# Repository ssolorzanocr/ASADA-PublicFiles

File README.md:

LoRa based control and log system for ASADA-Samara
============

### Most recent version of this repository can be found in: ###

* [ASADA-PublicFiles](https://github.com/ssolorzanocr/ASADA-PublicFiles)

### What is this repository for? ###

* This repository was created to develop LoRa based embedded control solution for the pumps of ASADA-Samara. 

### HELTEC LoRa 32 board information

* [Documentation page](https://heltec.org/project/wifi-lora-32/)
* [Pinout diagram](https://resource.heltec.cn/download/WiFi_LoRa_32/WIFI_LoRa_32_V2.pdf)
* [Schematic](https://resource.heltec.cn/download/WiFi_LoRa_32/V2/WIFI_LoRa_32_V2(868-915).PDF)
* [ESP32 datasheet](https://www.espressif.com/sites/default/files/documentation/esp32_datasheet_en.pdf) 

### Enclousure

* [Page](https://www.se.com/es/es/product/NSYCRN33200P/spacial-crn-plain-door-with-mount.plate.-h300xw300xd200-ip66-ik10-ral7035../) 

### How do I get set up? ###

* Install Git
* Install Arduino IDE
* Install Heltec ESP32 Library in the Arduino Library Manager
Open Arduino IDE, then Select `Sketch`->`Include Library`->`Manage Libraries...`
Search `Heltec ESP32` and install it.
* Install Adafruit MQTT Library in the Arduino Library Manager
Open Arduino IDE, then Select `Sketch`->`Include Library`->`Manage Libraries...`
Search `Adafruit MQTT` and install it.

### Library source code and examples
* [Adafruit_MQTT_Library](https://github.com/adafruit/Adafruit_MQTT_Library)

### Contribution guidelines ###

* If you want to propose a review or need to modify the code for any reason first clone this [repository](https://github.com/ssolorzanocr/ASADA-PublicFiles) in your PC and create a new branch for your changes. Once your changes are complete and fully tested ask the administrator permission to push this new branch into the source.
* If you just want to do local changes instead you can download a zip version of the repository and do all changes locally in your PC. 

### Who do I talk to? ###

* [Juan J. Rojas](mailto:juan.rojas@itcr.ac.cr)
* [Sergio Solorzano](mailto:solorzanos117@gmail.com)

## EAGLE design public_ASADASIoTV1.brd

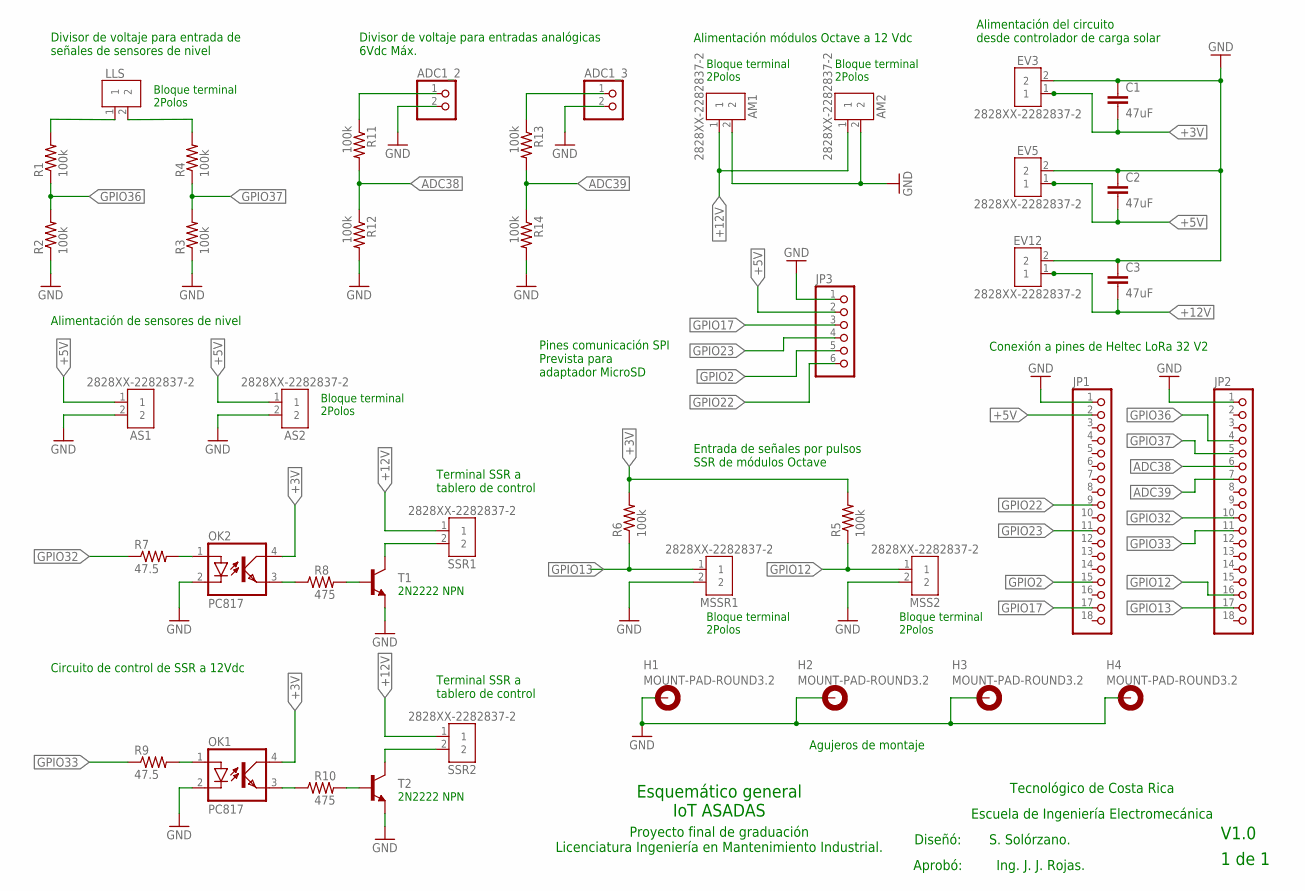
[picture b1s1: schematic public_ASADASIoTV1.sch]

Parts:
ADC1_2, ADC1_3: PINHD-1X2; 1X02
AM1, AM2: 2828XX-2282837-2; TERMBLK_508-2N
AS1, AS2: 2828XX-2282837-2; TERMBLK_508-2N
C1, C2, C3: 47uF; C2.5-5
EV3, EV5, EV12: 2828XX-2282837-2; TERMBLK_508-2N
H1, H2, H3, H4: MOUNT-PAD-ROUND3.2; 3,2-PAD
JP1, JP2: PINHD-1X18; 1X18
JP3: PINHD-1X6; 1X06
LLS: 2828XX-2282837-2; TERMBLK_508-2N
MSS2: 2828XX-2282837-2; TERMBLK_508-2N
MSSR1: 2828XX-2282837-2; TERMBLK_508-2N
OK1, OK2: PC817; DIL04
R1, R2, R3, R4, R5, R6, R11, R12, R13, R14: 100k; R0805
R7, R9: 47.5; R0805
R8, R10: 475; R0805
SSR1, SSR2: 2828XX-2282837-2; TERMBLK_508-2N
T1, T2: 2N3904; TO92

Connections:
+3V: C1.2, EV3.1, OK1.4 (COL), OK2.4 (COL), R5.2, R6.2
+5V: AS1.1, AS2.1, C2.2, EV5.1, JP1.2, JP3.2
+12V: AM1.1, AM2.1, C3.2, EV12.1, SSR1.1, SSR2.1
ADC38: JP2.6, R11.2, R12.1
ADC39: JP2.7, R13.2, R14.1
GND: ADC1_2.2, ADC1_3.2, AM1.2, AM2.2, AS1.2, AS2.2, C1.1, C2.1, C3.1, EV3.2, EV5.2, EV12.2, H1.B3,2, H2.B3,2, H3.B3,2, H4.B3,2, JP1.1, JP2.1, JP3.1, MSS2.2, MSSR1.2, OK1.2 (C), OK2.2 (C), R2.1, R3.1, R12.2, R14.2, T1.3 (E), T2.3 (E)
GPIO2: JP1.15, JP3.5
GPIO12: JP2.16, MSS2.1, R5.1
GPIO13: JP2.17, MSSR1.1, R6.1
GPIO17: JP1.17, JP3.3
GPIO22: JP1.9, JP3.6
GPIO23: JP1.11, JP3.4
GPIO32: JP2.10, R7.1
GPIO33: JP2.11, R9.1
GPIO36: JP2.4, R1.1, R2.2
GPIO37: JP2.5, R3.2, R4.1
HLS: LLS.2, R4.2
LLS: LLS.1, R1.2
unnamed: OK2.1 (A), R7.2
unnamed: SSR1.2, T1.1 (C)
unnamed: R8.2, T1.2 (B)
unnamed: OK2.3 (EMIT), R8.1
unnamed: ADC1_3.1, R13.1
unnamed: ADC1_2.1, R11.1
unnamed: OK1.1 (A), R9.2
unnamed: R10.2, T2.2 (B)
unnamed: OK1.3 (EMIT), R10.1
unnamed: SSR2.2, T2.1 (C)

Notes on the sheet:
Terminal SSR a tablero de control
Entrada de señales por pulsos SSR de módulos Octave
Alimentación de sensores de nivel
Divisor de voltaje para entrada de señales de sensores de nivel
Alimentación módulos Octave a 12 Vdc
Divisor de voltaje para entradas analógicas 6Vdc Máx.
Alimentación del circuito desde controlador de carga solar
Pines comunicación SPI Prevista para adaptador MicroSD
Agujeros de montaje
Conexión a pines de Heltec LoRa 32 V2
Circuito de control de SSR a 12Vdc
V1.0
1 de 1
Proyecto final de graduación Licenciatura Ingeniería en Mantenimiento Industrial.
Diseñó:
S. Solórzano.
Aprobó:
Ing. J. J. Rojas.
Escuela de Ingeniería Electromecánica
Tecnológico de Costa Rica
Esquemático general IoT ASADAS
2N2222 NPN
Bloque terminal 2Polos

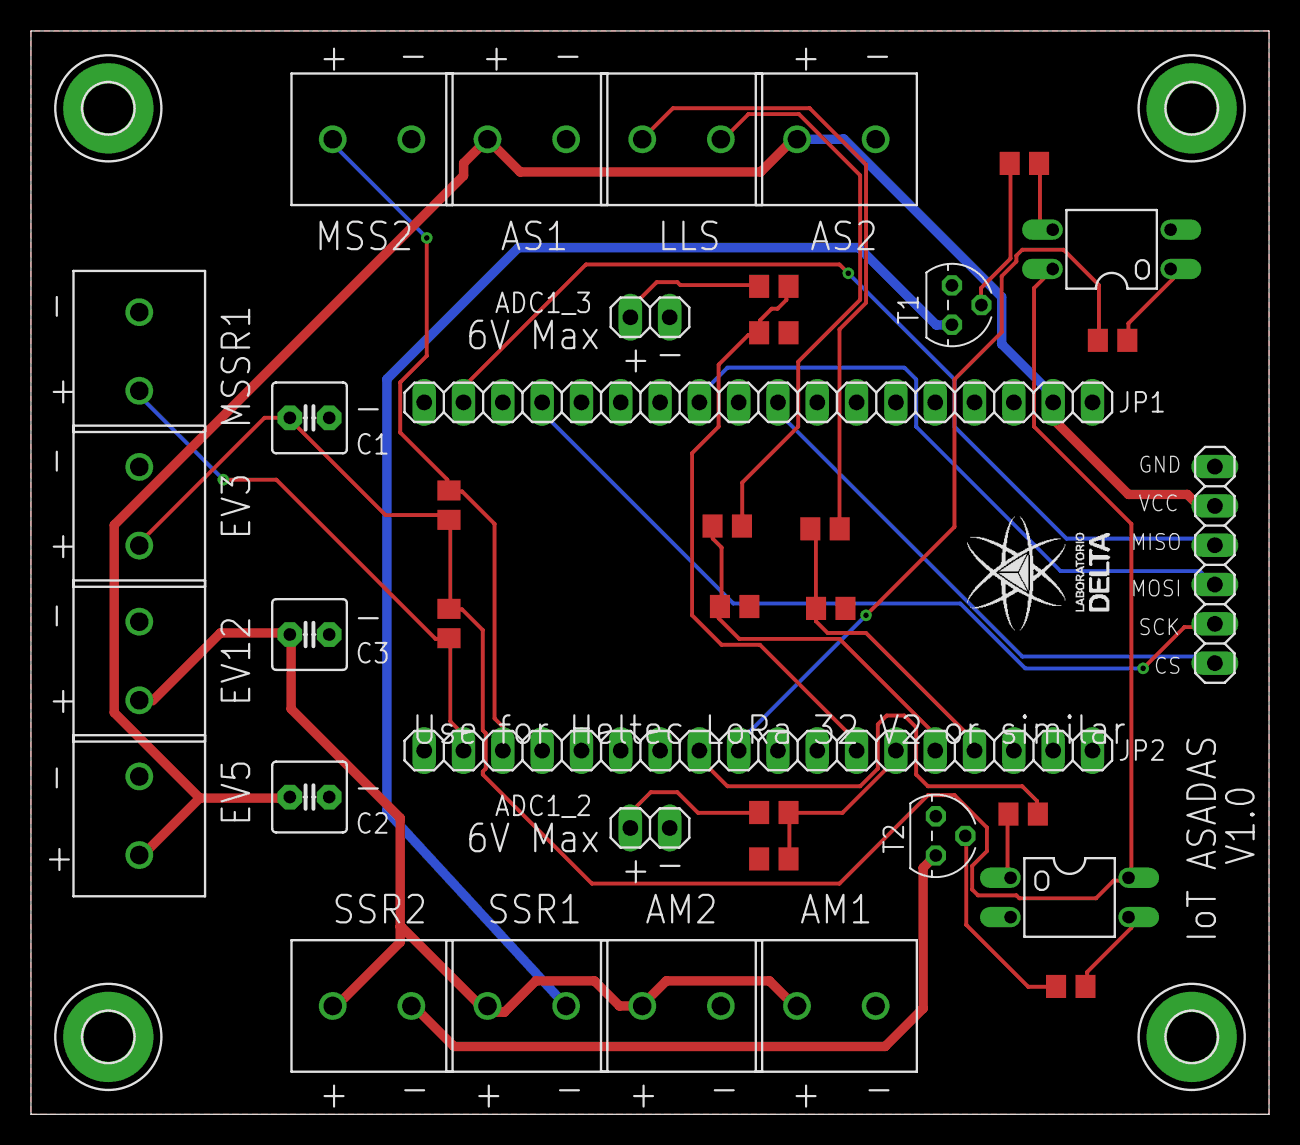
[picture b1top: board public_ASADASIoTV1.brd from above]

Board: 2 copper layers, 80.0 x 70.0 mm, 42 parts (0 on the bottom side), 28 nets.

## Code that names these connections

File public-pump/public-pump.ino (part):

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#define BAND    915E6   //you can set band here directly,e.g. 868E6 (Europe),915E6 (North America),433E6 (Asia)

//Micro TF card pins to ESP32 GPIOs via this connecthin:
#define SD_CS   22        //  SD_CS   -- GPIO22
#define SD_SCK  2         //  SD_SCK  -- GPIO2
#define SD_MOSI 23        //  SD_MOSI -- GPIO23
#define SD_MISO 17        //  SD_MISO -- GPIO17

#define DIGITAL_PULSE_1 13  //for hidric measures  
#define DIGITAL_PULSE_2 12  //for hidric measures
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  pinMode(DIGITAL_PULSE_1, INPUT_PULLUP); pinMode(DIGITAL_PULSE_2, INPUT_PULLUP); 
  pinMode(DIGITAL_SSROUT_1,OUTPUT); pinMode(DIGITAL_SSROUT_2,OUTPUT);
  pinMode(DIGITAL_INPUT_1,INPUT); pinMode(DIGITAL_INPUT_2,INPUT);
  attachInterrupt(DIGITAL_PULSE_1,&pulsecountA,RISING);      //(Interrupción (GPIO13),función,Flanco de subida)
  attachInterrupt(DIGITAL_PULSE_2,&pulsecountB,RISING);
  
  /* 1 tick take 1/(80MHZ/80) = 1us so we set divider 80 and count up */
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
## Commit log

2021-05-15 Files set free
2021-05-15 PCB design set free
